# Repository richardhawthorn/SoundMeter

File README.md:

### Description

PCB and Arduino code for a sound level meter.  Can be used as a spectrum analyser, or as a scrolling sound level meter.

### Features

- Bi-colour 8x8 LED matrix
- Microphone and built in amplifier
- ATMEGA328P with Arduino boot-loader
- 5V operation @ 16Mhz
- Mini USB power connector
- FTDI programming port
- ICSP port

### License

This work is licensed under a Creative Commons Attribution-ShareAlike 4.0 International License.

<br />
Designed by <a xmlns:cc="http://creativecommons.org/ns#" href="http://www.richardhawthorn.com" property="cc:attributionName" rel="cc:attributionURL" target="_blank">Richard Hawthorn</a><br />
<a rel="license" href="http://creativecommons.org/licenses/by-sa/4.0/" target="_blank">View License</a>

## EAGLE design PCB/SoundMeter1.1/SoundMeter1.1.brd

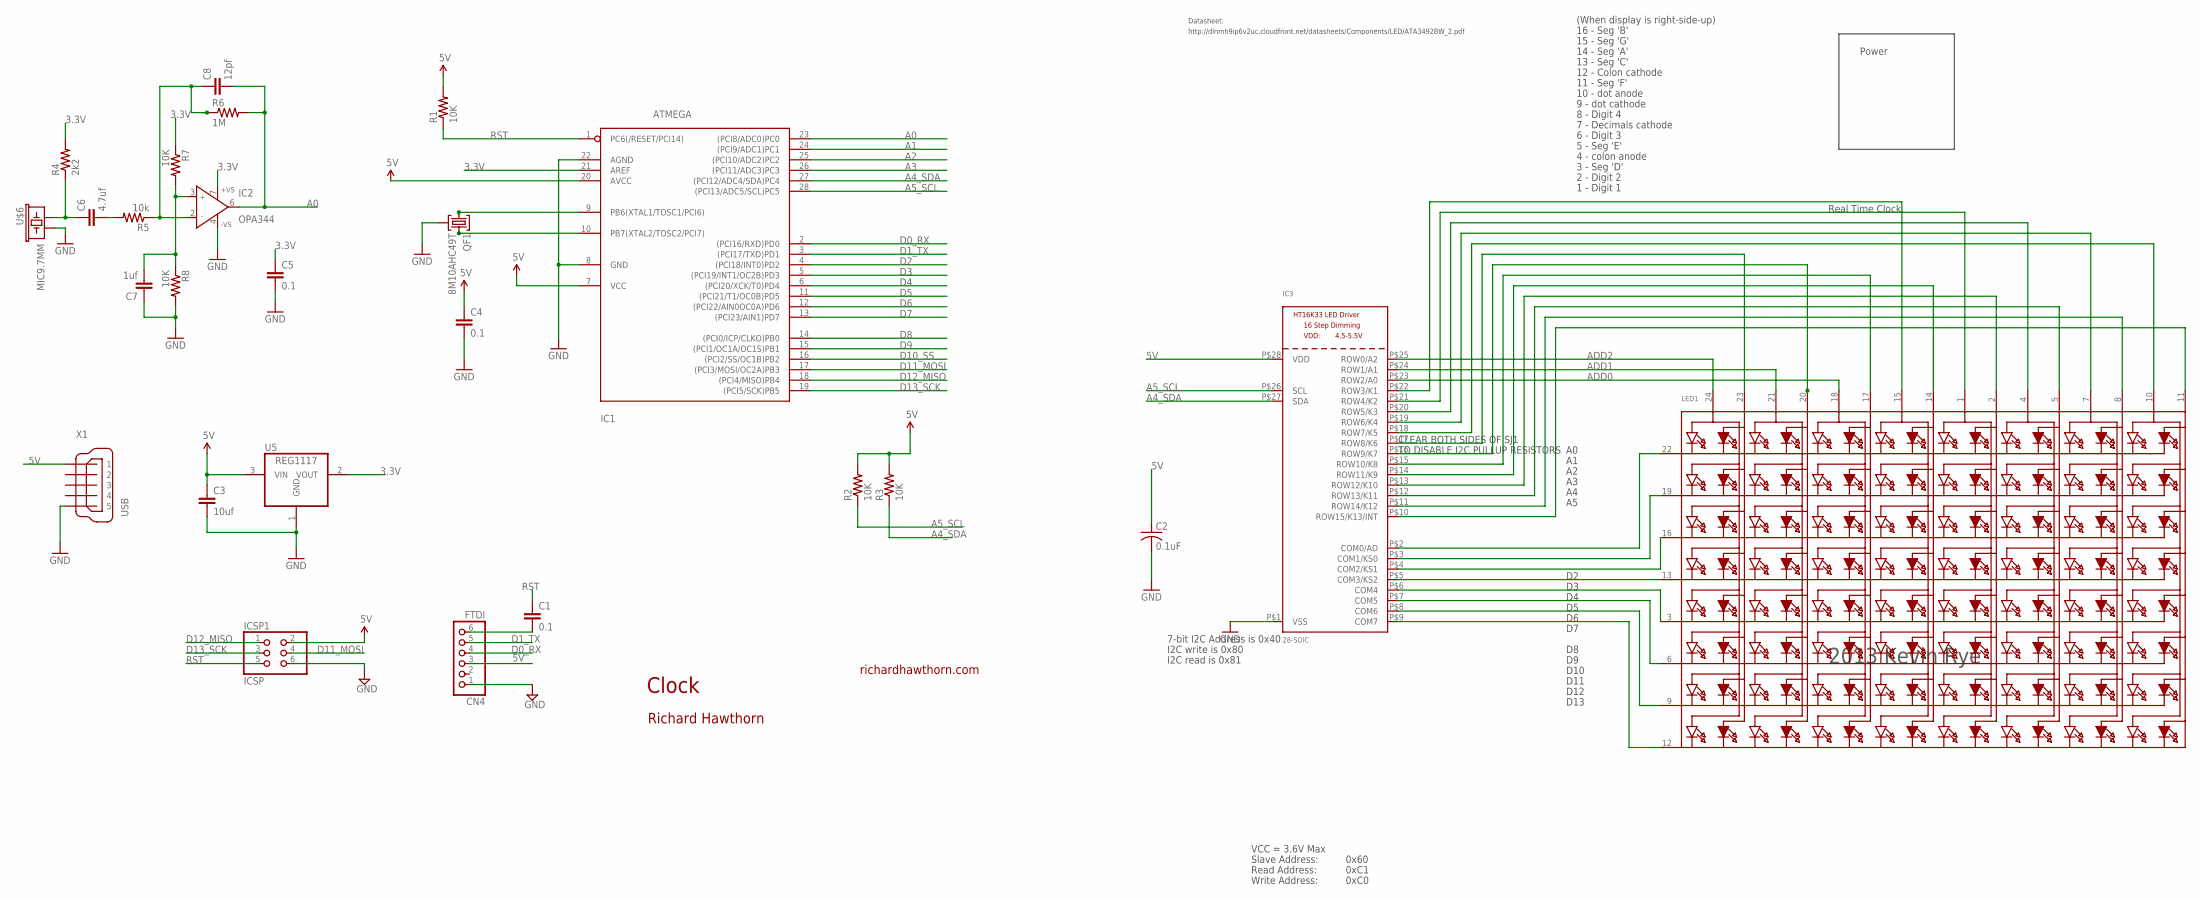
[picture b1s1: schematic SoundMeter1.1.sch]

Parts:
C1, C4, C5: 0.1; CAP-PTH-SMALL2
C2: 0.1uF; C025-025X050
C3: 10uf; CAP-PTH-SMALL2
C6: 4.7uf; CAP-PTH-SMALL2
C7: 1uf; CAP-PTH-SMALL2
C8: 12pf; CAP-PTH-SMALL2
CN4: FTDI; 1X06
IC1: ATMEGA; DIL28-3-ROUND
IC2: OPA344; DIL08
IC3: 28-SOIC; SOP28_300MIL
ICSP1: ICSP; 2X03
LED1: DISP_SEGMENT_8X8_BICOLOR_ROWCATHODEMI2A883XX; SEGMENT_BICOL_BL-M12A883XX
QF1: 8M10AHC49T; HC49U
R1, R2, R3, R7, R8: 10K; 0204/7
R4: 2k2; 0204/7
R5: 10k; 0204/7
R6: 1M; 0204/7
U5: REG1117; SOT223
U$6: MIC9.7MM; MIC-9.7MM
X1: USB; 32005-601

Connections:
3.3V: C5.1, IC1.21 (AREF), IC2.7 (+VS), R4.2, R7.1, U5.2 (VOUT)
5V: C2.1, C3.1, C4.1, CN4.3, IC1.7 (VCC), IC1.20 (AVCC), IC3.P$28 (VDD), ICSP1.2, R1.2, R2.2, R3.2, U5.3 (VIN), X1.1
A0: C8.2, IC1.23 ((PCI8/ADC0)PC0), IC2.6 (OUT), R6.2
A1: IC1.24 ((PCI9/ADC1)PC1)
A2: IC1.25 ((PCI10/ADC2)PC2)
A3: IC1.26 ((PCI11/ADC3)PC3)
A4_SDA: IC1.27 ((PCI12/ADC4/SDA)PC4), IC3.P$27 (SDA), R3.1
A5_SCL: IC1.28 ((PCI13/ADC5/SCL)PC5), IC3.P$26 (SCL), R2.1
ADD0: IC3.P$23 (ROW2/A0), LED1.18 (A5)
ADD1: IC3.P$24 (ROW1/A1), LED1.21 (A3)
ADD2: IC3.P$25 (ROW0/A2), LED1.24 (A1)
COM: IC3.P$2 (COM0/AD), LED1.22 (K1)
D0_RX: CN4.4, IC1.2 ((PCI16/RXD)PD0)
D1_TX: CN4.5, IC1.3 ((PCI17/TXD)PD1)
D2: IC1.4 ((PCI18/INT0)PD2)
D3: IC1.5 ((PCI19/INT1/OC2B)PD3)
D4: IC1.6 ((PCI20/XCK/T0)PD4)
D5: IC1.11 ((PCI21/T1/OC0B)PD5)
D6: IC1.12 ((PCI22/AIN0OC0A)PD6)
D7: IC1.13 ((PCI23/AIN1)PD7)
D8: IC1.14 ((PCI0/ICP/CLKO)PB0)
D9: IC1.15 ((PCI1/OC1A/OC1S)PB1)
D10_SS: IC1.16 ((PCI2/SS/OC1B)PB2)
D11_MOSI: IC1.17 ((PCI3/MOSI/OC2A)PB3), ICSP1.4
D12_MISO: IC1.18 ((PCI4/MISO)PB4), ICSP1.1
D13_SCK: IC1.19 ((PCI5/SCK)PB5), ICSP1.3
GND: C2.2, C3.2, C4.2, C5.2, C7.1, CN4.1, IC1.8 (GND), IC1.22 (AGND), IC2.4 (-VS), IC3.P$1 (VSS), ICSP1.6, QF1.2, R8.2, U5.1 (GND), U$6.2, X1.5
unnamed: C6.2, R5.2
unnamed: IC3.P$9 (COM7), LED1.12 (K8)
unnamed: C8.1, IC2.2 (IN-), R5.1, R6.1
unnamed: IC3.P$8 (COM6), LED1.9 (K7)
unnamed: C6.1, R4.1, U$6.1
unnamed: C7.2, IC2.3 (IN+), R7.2, R8.1
unnamed: IC3.P$7 (COM5), LED1.6 (K6)
unnamed: IC3.P$6 (COM4), LED1.3 (K5)
unnamed: IC3.P$5 (COM3/KS2), LED1.13 (K4)
unnamed: IC3.P$4 (COM2/KS1), LED1.16 (K3)
unnamed: IC3.P$3 (COM1/KS0), LED1.19 (K2)
unnamed: IC3.P$11 (ROW14/K12), LED1.8 (A14)
unnamed: IC3.P$12 (ROW13/K11), LED1.5 (A12)
unnamed: IC1.9 (PB6(XTAL1/TOSC1/PCI6)), QF1.1
unnamed: C1.2, CN4.6
unnamed: IC3.P$18 (ROW7/K5), LED1.10 (A15)
unnamed: IC3.P$19 (ROW6/K4), LED1.7 (A13)
unnamed: IC1.10 (PB7(XTAL2/TOSC2/PCI7)), QF1.3
unnamed: IC3.P$21 (ROW4/K2), LED1.1 (A9)
unnamed: IC3.P$22 (ROW3/K1), LED1.15 (A7)
unnamed: IC3.P$10 (ROW15/K13/INT), LED1.11 (A16)
unnamed: IC3.P$20 (ROW5/K3), LED1.4 (A11)
unnamed: IC3.P$17 (ROW8/K6), LED1.23 (A2)
unnamed: IC3.P$16 (ROW9/K7), LED1.20 (A4)
unnamed: IC3.P$14 (ROW11/K9), LED1.14 (A8)
unnamed: IC3.P$15 (ROW10/K8), LED1.17 (A6)
unnamed: IC3.P$13 (ROW12/K10), LED1.2 (A10)
RST: C1.1, IC1.1 (PC6(/RESET/PCI14)), ICSP1.5, R1.1

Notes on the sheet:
Clock
richardhawthorn.com
Richard Hawthorn
CLEAR BOTH SIDES OF SJ1
TO DISABLE I2C PULLUP RESISTORS
7-bit I2C Address is 0x40
I2C write is 0x80
I2C read is 0x81
VCC = 3.6V Max
Read Address:
Write Address:
Slave Address:
0x60
0xC1
0xC0
14 - Seg 'A'
13 - Seg 'C'
12 - Colon cathode
11 - Seg 'F'
10 - dot anode
9 - dot cathode
8 - Digit 4
7 - Decimals cathode
6 - Digit 3
5 - Seg 'E'
4 - colon anode
3 - Seg 'D'
2 - Digit 2
Real Time Clock
1 - Digit 1
15 - Seg 'G'
16 - Seg 'B'
D10
D11
D12
D13
http://dlnmh9ip6v2uc.cloudfront.net/datasheets/Components/LED/ATA3492BW_2.pdf
Datasheet:
Power
(When display is right-side-up)

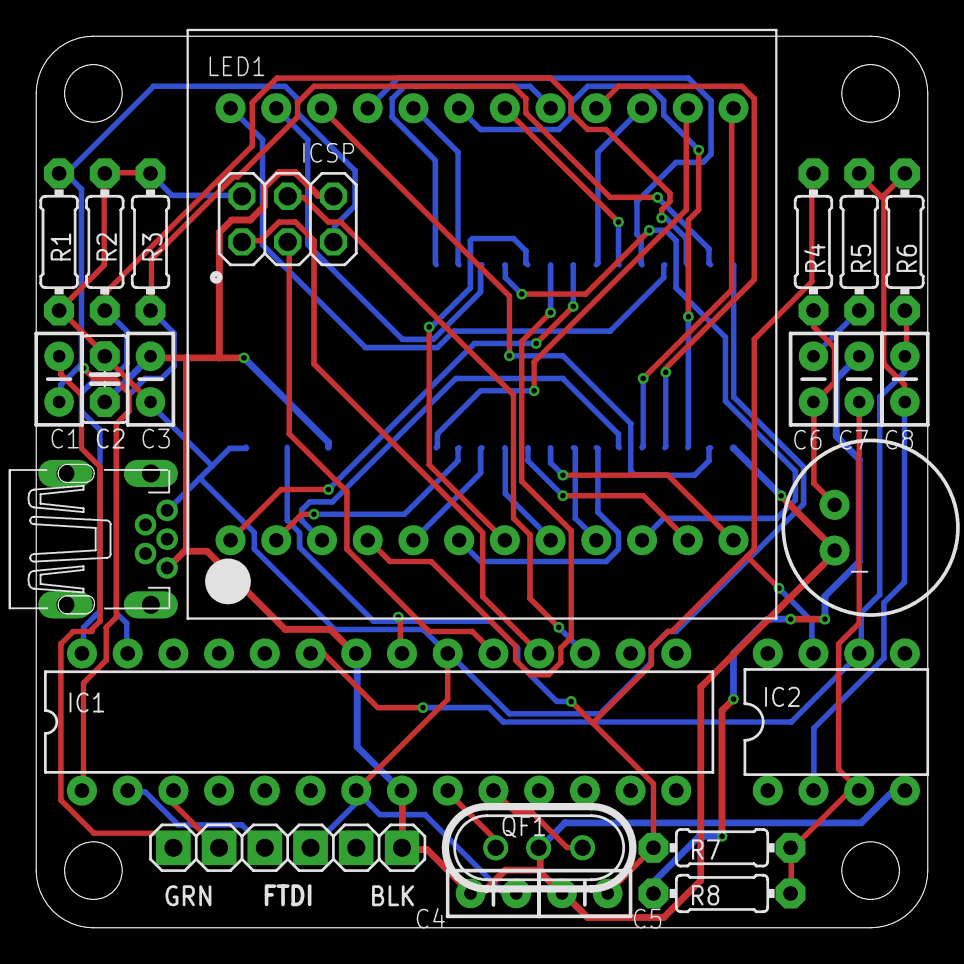
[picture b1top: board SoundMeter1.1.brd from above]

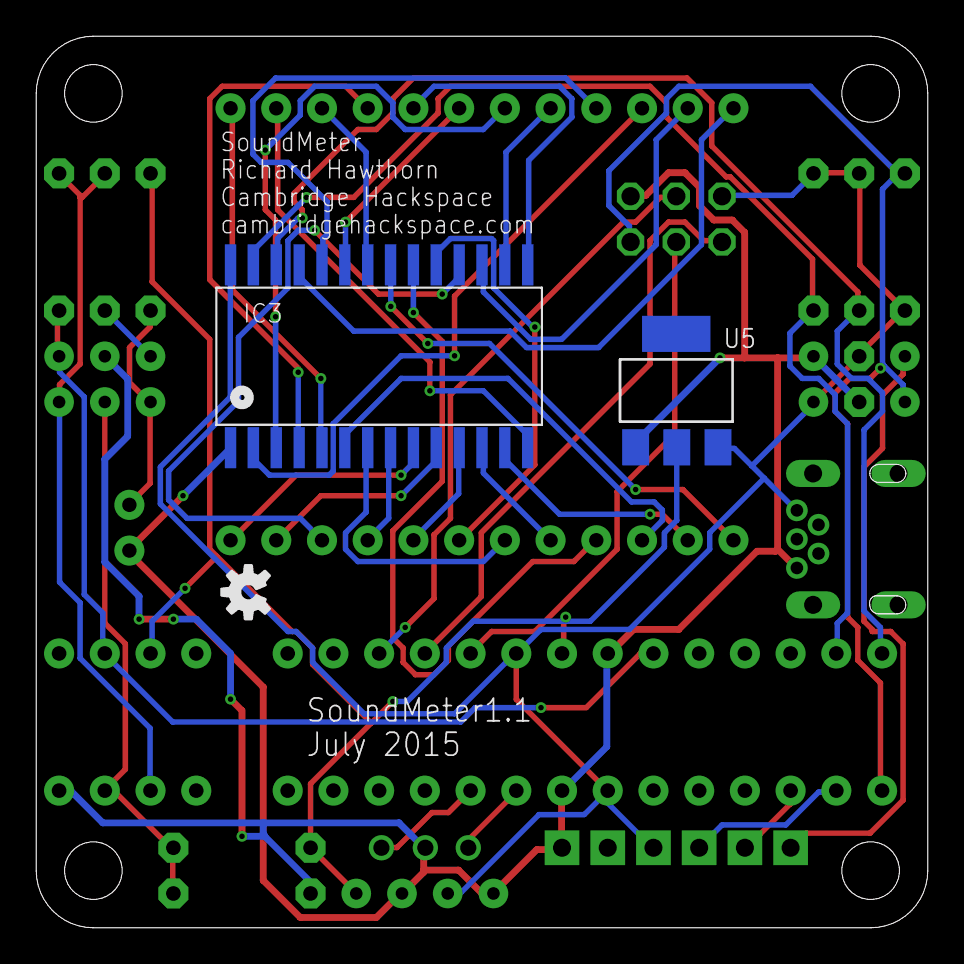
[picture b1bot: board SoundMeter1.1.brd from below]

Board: 2 copper layers, 49.5 x 49.5 mm, 27 parts (3 on the bottom side), 43 nets.

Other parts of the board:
U$3: OSHW-LOGO-S

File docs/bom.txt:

Qty Value      Device                                       Package                    Parts              Description                                                    
1              DISP_SEGMENT_8X8_BICOLOR                     SEGMENT_BICOL              LED1               8x8 Bi-Color LED Segment Displays: Row = Cathode               
3   0.1uf      CAPPTH2                                      CAP-PTH-SMALL2             C1, C2, C4, C5     Capacitor                                                                                          
5   10K        R-US_0204/7                                  0204/7                     R1, R2, R3, R7, R8 RESISTOR, American symbol                                      
1   10k        R-US_0204/7                                  0204/7                     R5                 RESISTOR, American symbol                                      
1   10uf       CAPPTH2                                      CAP-PTH-SMALL2             C3                 Capacitor                                                      
1   12pf       CAPPTH2                                      CAP-PTH-SMALL2             C8                 Capacitor                                                      
1   1M         R-US_0204/7                                  0204/7                     R6                 RESISTOR, American symbol                                      
1   1uf        CAPPTH2                                      CAP-PTH-SMALL2             C7                 Capacitor                                                      
1   28-SOIC    HT16K33_SOP28                                SOP28_300MIL               IC3                                                                               
1   2k2        R-US_0204/7                                  0204/7                     R4                 RESISTOR, American symbol                                      
1   4.7uf      CAPPTH2                                      CAP-PTH-SMALL2             C6                 Capacitor                                                      
1   8M10AHC49T 8M10AHC49T                                   HC49U                      QF1                Monolithic Crystal Filters                                     
1   ATMEGA     ATMEGA168PROUND                              DIL28-3-ROUND              IC1                MICROCONTROLLER                                                
1   FTDI       PINHD-1X6                                    1X06                       CN4                PIN HEADER                                                     
1   ICSP       PINHD-2X3                                    2X03                       ICSP1              PIN HEADER                                                     
1   MIC9.7MM   MIC9.7MM                                     MIC-9.7MM                  U$6                Omni-directional electret microphone. 9.7mm standard diameter. 
1   OPA344     OPA344                                       DIL08                      IC2                OPA344                                                         
1   REG1117    REG1117                                      SOT223                     U5                 800mA and 1A Low Dropout (LDO) Positive Regulator              
1   USB        MINI-USB_SHIELD5P2-32005-601                 32005-601                  X1                 MINI USB-B R/A DIP 5pol.

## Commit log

2015-08-08 add readme
2015-08-08 add pcb and images
2015-08-08 add bom and code examples
2016-01-02 add images

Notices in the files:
parts and their libraries:
SparkFun-Aesthetics: Licensing: CC v3.0 Share-Alike You are welcome to use this library for commercial purposes.
SparkFun-Sensors: Licensing: Creative Commons ShareAlike 4.0 International - https://creativecommons.org/licenses/by-sa/4.0
